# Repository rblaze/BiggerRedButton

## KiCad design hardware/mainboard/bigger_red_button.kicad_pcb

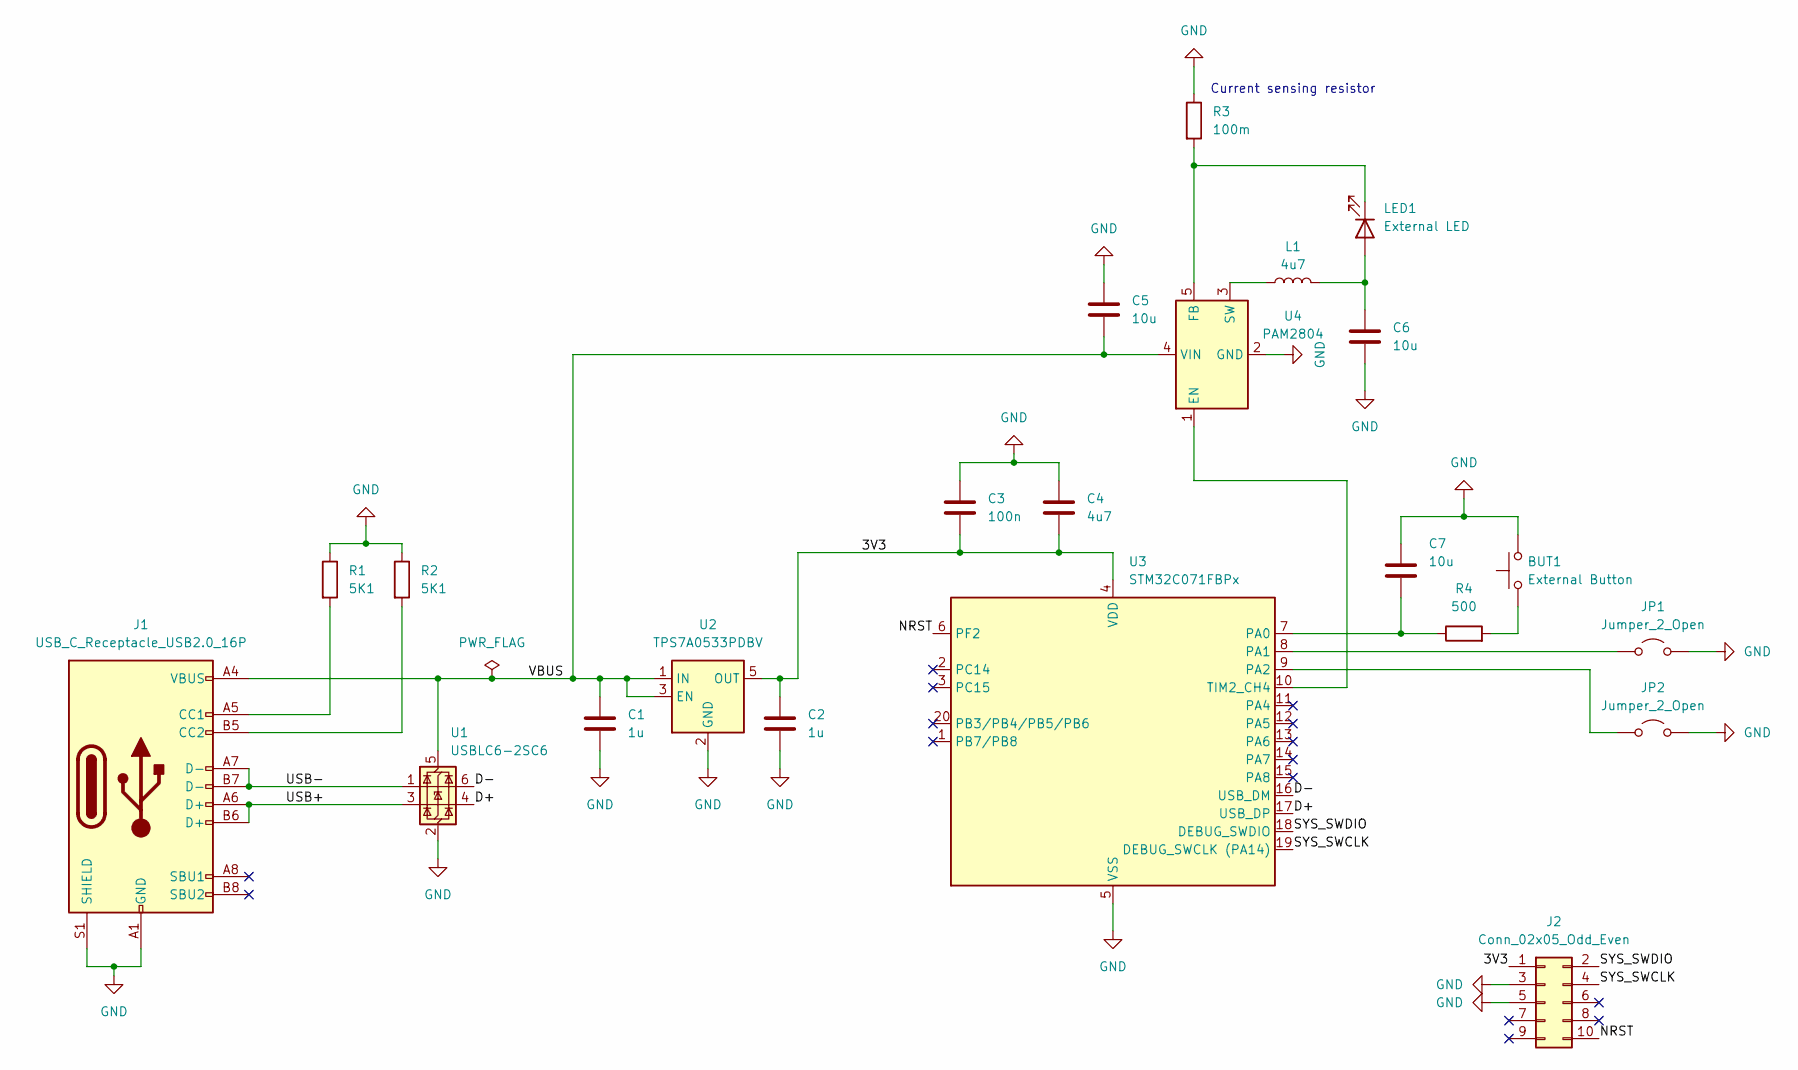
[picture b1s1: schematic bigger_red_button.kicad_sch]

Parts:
BUT1: External Button; PinHeader_1x02_P2.54mm_Vertical
C1, C2: 1u; C_0402_1005Metric; LCSC Part # C52923
C3: 100n; C_0402_1005Metric; LCSC Part # C1525
C4: 4u7; C_0402_1005Metric; LCSC Part # C23733
C5, C6, C7: 10u; C_0402_1005Metric; LCSC Part # C15525
J1: USB_C_Receptacle_USB2.0_16P; USB_C_Receptacle_GCT_USB4105-xx-A_16P_TopMnt_Horizontal; LCSC Part # C165948
J2: Conn_02x05_Odd_Even; SAMTEC_FTSH-105-XX-X-DV; LCSC Part # C448647
JP1, JP2: Jumper_2_Open; PinHeader_1x02_P2.54mm_Vertical
L1: 4u7; L_1008_2520Metric
LED1: External LED; PinHeader_1x02_P2.54mm_Vertical
R1, R2: 5K1; R_0402_1005Metric; LCSC Part # C25905
R3: 100m; R_1206_3216Metric; LCSC Part # C25334
R4: 500; R_0402_1005Metric; LCSC Part # C25123
U1: USBLC6-2SC6; SOT-23-6; LCSC Part # C7519
U2: TPS7A0533PDBV; SOT-23-5; LCSC Part # C2862740
U3: STM32C071FBPx; TSSOP-20_4.4x6.5mm_P0.65mm
U4: PAM2804; TSOT-23-5; LCSC Part # C71463

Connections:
/3V3: C2.1, C3.2, C4.2, J2.1, U2.5 (OUT), U3.4 (VDD)
/D+: U1.4 (I/O2), U3.17 (USB_DP)
/D-: U1.6 (I/O1), U3.16 (USB_DM)
/NRST: J2.10, U3.6 (PF2)
/SYS_SWCLK: J2.4, U3.19 (DEBUG_SWCLK (PA14))
/SYS_SWDIO: J2.2, U3.18 (DEBUG_SWDIO)
/USB+: J1.A6 (D+), J1.B6 (D+), U1.3 (I/O2)
/USB-: J1.A7 (D-), J1.B7 (D-), U1.1 (I/O1)
/VBUS: C1.1, C5.2, J1.A4 (VBUS), J1.A9 (VBUS), J1.B4 (VBUS), J1.B9 (VBUS), U1.5 (VBUS), U2.1 (IN), U2.3 (EN), U4.4 (VIN)
GND: BUT1.2, C1.2, C2.2, C3.1, C4.1, C5.1, C6.2, C7.1, J1.A1 (GND), J1.A12 (GND), J1.B1 (GND), J1.B12 (GND), J1.S1 (SHIELD), J2.3, J2.5, JP1.2 (B), JP2.2 (B), R1.1, R2.1, R3.1, U1.2 (GND), U2.2 (GND), U3.5 (VSS), U4.2 (GND)
unnamed: BUT1.1, R4.2
unnamed: J1.A5 (CC1), R1.2
unnamed: J1.B5 (CC2), R2.2
unnamed: JP1.1 (A), U3.8 (PA1)
unnamed: JP2.1 (A), U3.9 (PA2)
unnamed: C6.1, L1.2, LED1.2 (A)
unnamed: LED1.1 (K), R3.2, U4.5 (FB)
unnamed: C7.2, R4.1, U3.7 (PA0)
unnamed: U3.10 (TIM2_CH4), U4.1 (EN)
unnamed: L1.1, U4.3 (SW)

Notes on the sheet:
Current sensing resistor

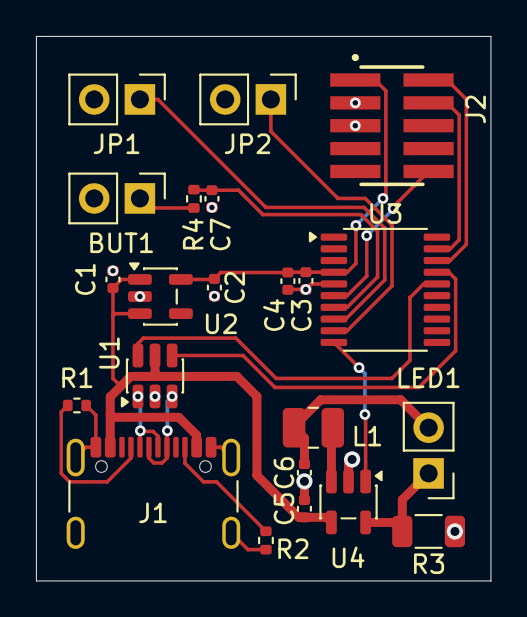
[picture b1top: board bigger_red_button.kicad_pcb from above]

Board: 2 copper layers, 25.2 x 30.2 mm, 22 parts (0 on the bottom side), 20 nets.

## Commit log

2025-03-02 Initial code generation
2025-03-02 Blink LED for one second when button is pressed
2025-03-07 Add USB keyboard reports
2025-03-07 Blink LED 3 times
2025-11-23 Replace MCU with STM32C071 in CubeMX project
2025-11-30 Update .gitignore with new generated files
2025-12-06 Implement Big Red Button for STM32C0
    Not tested, pending hardware readyness
2025-12-30 Move hardware projects from misc_pcbs
2026-01-23 USB keyboard detected
2026-01-23 USB keyboard works on windows
2026-01-23 Interrupt-based event loop
2026-01-24 Fix PWM frequency, now 500Hz
2026-01-24 Fix timer channel for blinking
